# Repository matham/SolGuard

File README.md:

# SolGuard

This boards acts like a [snubber](https://en.wikipedia.org/wiki/Snubber) that prevents collapsing fields
of solenoids from disrupting surrounding electronics.

When using a relay board, such as the [MOD-IO](https://www.olimex.com/Products/Modules/IO/MOD-IO/open-source-hardware),
with a Raspberry Pi we found that switching the valves would periodically break the communication between the Pi
and the board. This is due to the transient currents disrupting surrounding and connected electronics.

This board uses a `RC` circuit plus a `diode` to prevent these sudden transients and to prevent over-voltage on the
power rails.

The diodes and RC components used determine the maximum input voltage supported. The ones below support
solenoids up to `35VDC`.

## Bill of materials

| Quantity | Description                     | DigiKey #                 | MFG          | MFG #              | Alt`*` DigiKey #       |
|----------|---------------------------------|---------------------------|--------------|--------------------|------------------------|
| 1        | SolGuard PCB                    |                           | OSH Park     |                    |                        |
| 2        | TERM BLK 2P SIDE ENT 5.08MM PCB | 277-15491-ND              | PHOENIX CON. | 5452257            | 5430360-ND             |
| 1        | DIODE GEN PURP 100V 500MA DO35  | 1N4149CT-ND               | ONSEMI       | 1N4149TR           | 1N4149CT-ND            |
| 1        | RES 300 OHM 1% 5W AXIAL         | 696-1078-ND               | BE SERVICES  | UB5C-300RF1        | RSC-300RCT-ND          |
| 1        | CAP ALUM POLY 470UF 20% 35V T/H | 399-A750MV477M1VAAE018-ND | KEMET        | A750MV477M1VAAE018 | 10-EEH-AZS1V471BCT-ND  |

The PCB (`SolGuard.kicad_pcb`) was manufactured by OSH Park using their with the following specs:

    0.52 x 1.72 inch (13.3 x 43.8 mm) 2 layer board.

`*`These are DigiKey part numbers for alternate versions of these parts if the main one is not available.

## Build

To build, it's easiest to first solder the two terminals, the diode, the capacitor, and then the resistor.

## Usage

To use, on the solenoid side connect the two leads of the solenoid / valve. Typically, they are not sensitive to
polarity. On the other side, a typical construction is to connect the ground terminal to ground and the other terminal
to the relay's switching terminal.

For the relays terminals, the **normally closed** side is left unconnected, the
**normally open** side is connected to power, and the **switching** terminal to the SolGuard board's power terminal.
Then, by default, the valve is unpowered. But when the relay is ON, the switching terminal and the power side terminal
of the board is connected powering the solenoid.

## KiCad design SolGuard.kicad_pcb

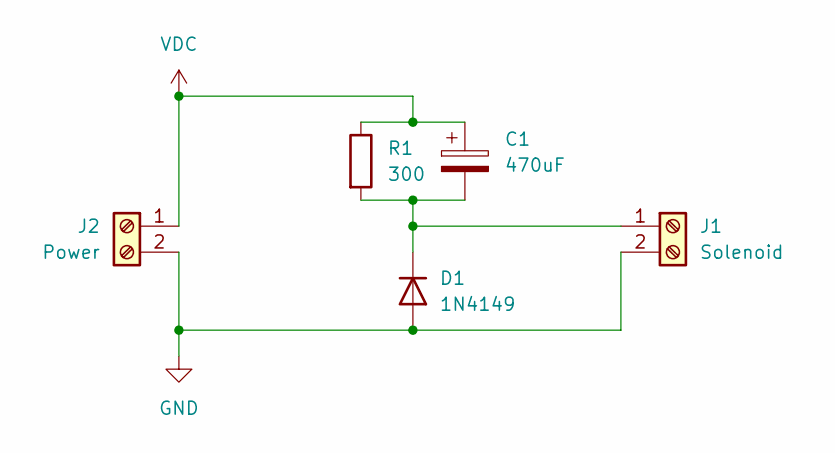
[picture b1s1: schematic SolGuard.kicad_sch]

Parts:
C1: 470uF; CP_Radial_D10.0mm_P5.00mm
D1: 1N4149; D_DO-35_SOD27_P7.62mm_Horizontal
J1: Solenoid; TerminalBlock_Phoenix_MKDS-1,5-2-5.08_1x02_P5.08mm_Horizont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
J2: Power; TerminalBlock_Phoenix_MKDS-1,5-2-5.08_1x02_P5.08mm_Horizont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
R1: 300; R_Axial_Power_L20.0mm_W6.4mm_P7.62mm_Vertical

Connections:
GND: D1.2 (A), J1.2, J2.2
unnamed: C1.2, D1.1 (K), J1.1, R1.2
VDC: C1.1, J2.1, R1.1

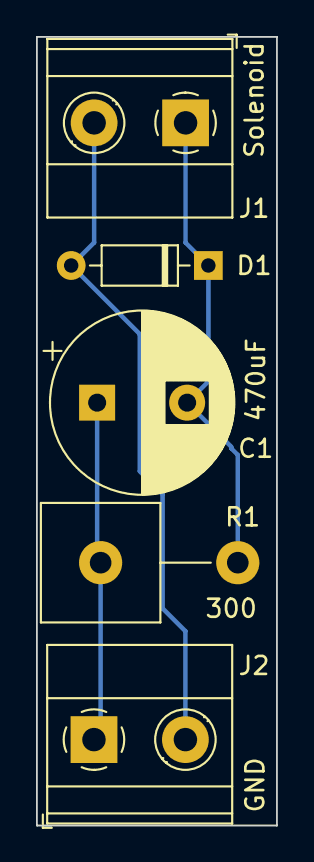
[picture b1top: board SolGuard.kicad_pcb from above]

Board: 2 copper layers, 13.3 x 43.8 mm, 5 parts (0 on the bottom side), 3 nets.

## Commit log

2025-03-28 Add some docs.
